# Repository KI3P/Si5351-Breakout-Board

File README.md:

This repository contains the KiCad files for an Si5351 breakout board. It uses the Si5351A-B-GM in a QFN form factor to obtain 8 clock outputs. It is suitable for retrofitting a T41-EP V12 RF board to obtain separate RX and TX VFOs.

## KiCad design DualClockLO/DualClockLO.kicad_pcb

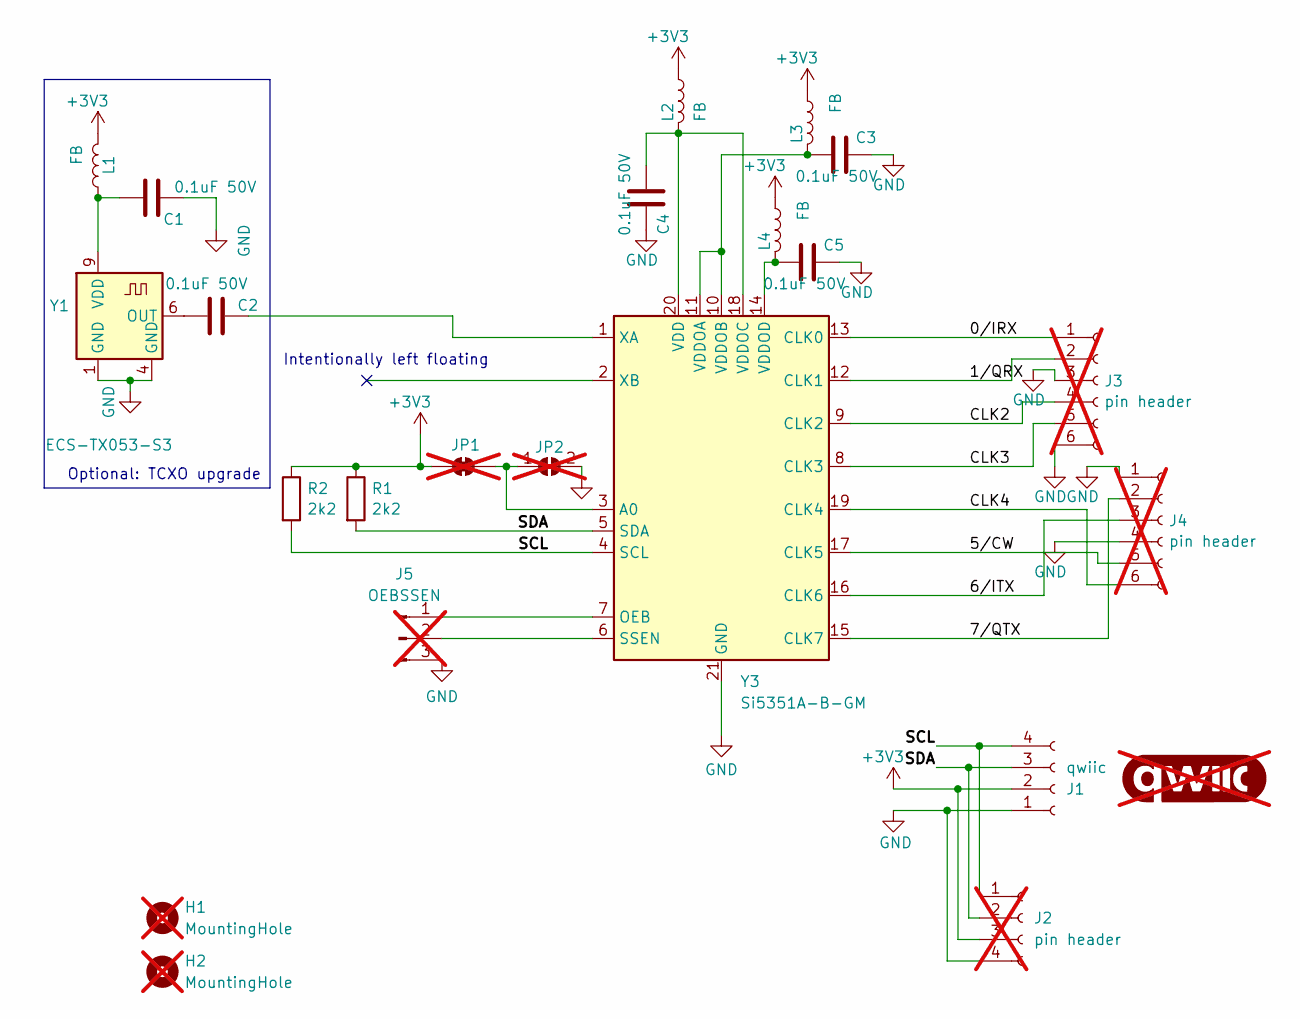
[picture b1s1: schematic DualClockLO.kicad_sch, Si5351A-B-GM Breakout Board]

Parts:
C1, C2, C3, C4, C5: 0.1uF 50V; C_0603_1608Metric
G1: qwiic_Logo; qwiic_4mm; not fitted
H1, H2: MountingHole; MountingHole_2.2mm_M2_DIN965; not fitted
J1: qwiic; JST_SH_SM04B-SRSS-TB_1x04-1MP_P1.00mm_Horizontal
J2: pin header; PinHeader_1x04_P2.54mm_Vertical; not fitted
J3, J4: pin header; PinHeader_1x06_P2.54mm_Vertical; not fitted
J5: OEBSSEN; PinHeader_1x03_P2.54mm_Vertical; not fitted
JP1: GND select; SolderJumper-2_P1.3mm_Bridged_RoundedPad1.0x1.5mm; not fitted
JP2: SolderJumper_2_Open; SolderJumper-2_P1.3mm_Open_TrianglePad1.0x1.5mm; not fitted
L1, L2, L3, L4: FB; L_0603_1608Metric
R1, R2: 2k2; R_0603_1608Metric
Y1: ECS-TX053-S3; Oscillator_ECS_TXO53_S3
Y3: Si5351A-B-GM; QFN-20-1EP_4x4mm_P0.5mm_EP2.7x2.7mm

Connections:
+3V3: J1.2, J2.3, JP1.1 (A), L1.2, L2.1, L3.1, L4.1, R1.1, R2.1
/0/IRX: J3.1, Y3.13 (CLK0)
/1/QRX: J3.2, Y3.12 (CLK1)
/5/CW: J4.5, Y3.17 (CLK5)
/6/ITX: J4.3, Y3.16 (CLK6)
/7/QTX: J4.2, Y3.15 (CLK7)
/CLK2: J3.4, Y3.9 (CLK2)
/CLK3: J3.5, Y3.8 (CLK3)
/CLK4: J4.6, Y3.19 (CLK4)
/SCL: J1.4, J2.1, R2.2, Y3.4 (SCL)
/SDA: J1.3, J2.2, R1.2, Y3.5 (SDA)
GND: C1.2, C3.2, C4.2, C5.2, J1.1, J2.4, J3.3, J3.6, J4.1, J4.4, J5.3, JP2.2 (B), Y1.1 (GND), Y1.4 (GND), Y3.21 (GND)
unnamed: J5.1, Y3.7 (OEB)
unnamed: J5.2, Y3.6 (SSEN)
unnamed: JP1.2 (B), JP2.1 (A), Y3.3 (A0)
unnamed: C2.2, Y1.6 (OUT)
unnamed: C1.1, L1.1, Y1.9 (VDD)
unnamed: C4.1, L2.2, Y3.18 (VDDOC), Y3.20 (VDD)
unnamed: C3.1, L3.2, Y3.10 (VDDOB), Y3.11 (VDDOA)
unnamed: C5.1, L4.2, Y3.14 (VDDOD)
unnamed: C2.1, Y3.1 (XA)

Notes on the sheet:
Intentionally left floating
Optional: TCXO upgrade

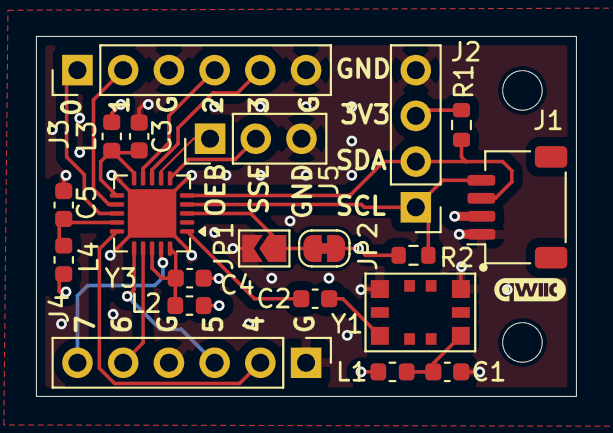
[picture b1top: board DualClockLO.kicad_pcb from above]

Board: 4 copper layers, 30.0 x 20.0 mm, 23 parts (0 on the bottom side), 21 nets.

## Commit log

2025-12-27 Initial revision 25NOV25
2025-12-29 Rev 2 modifications
